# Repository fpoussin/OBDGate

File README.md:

# OBDGate
ELM327 compatible interface for motorcycle diagnostic interfaces (Honda, Kawasaki)

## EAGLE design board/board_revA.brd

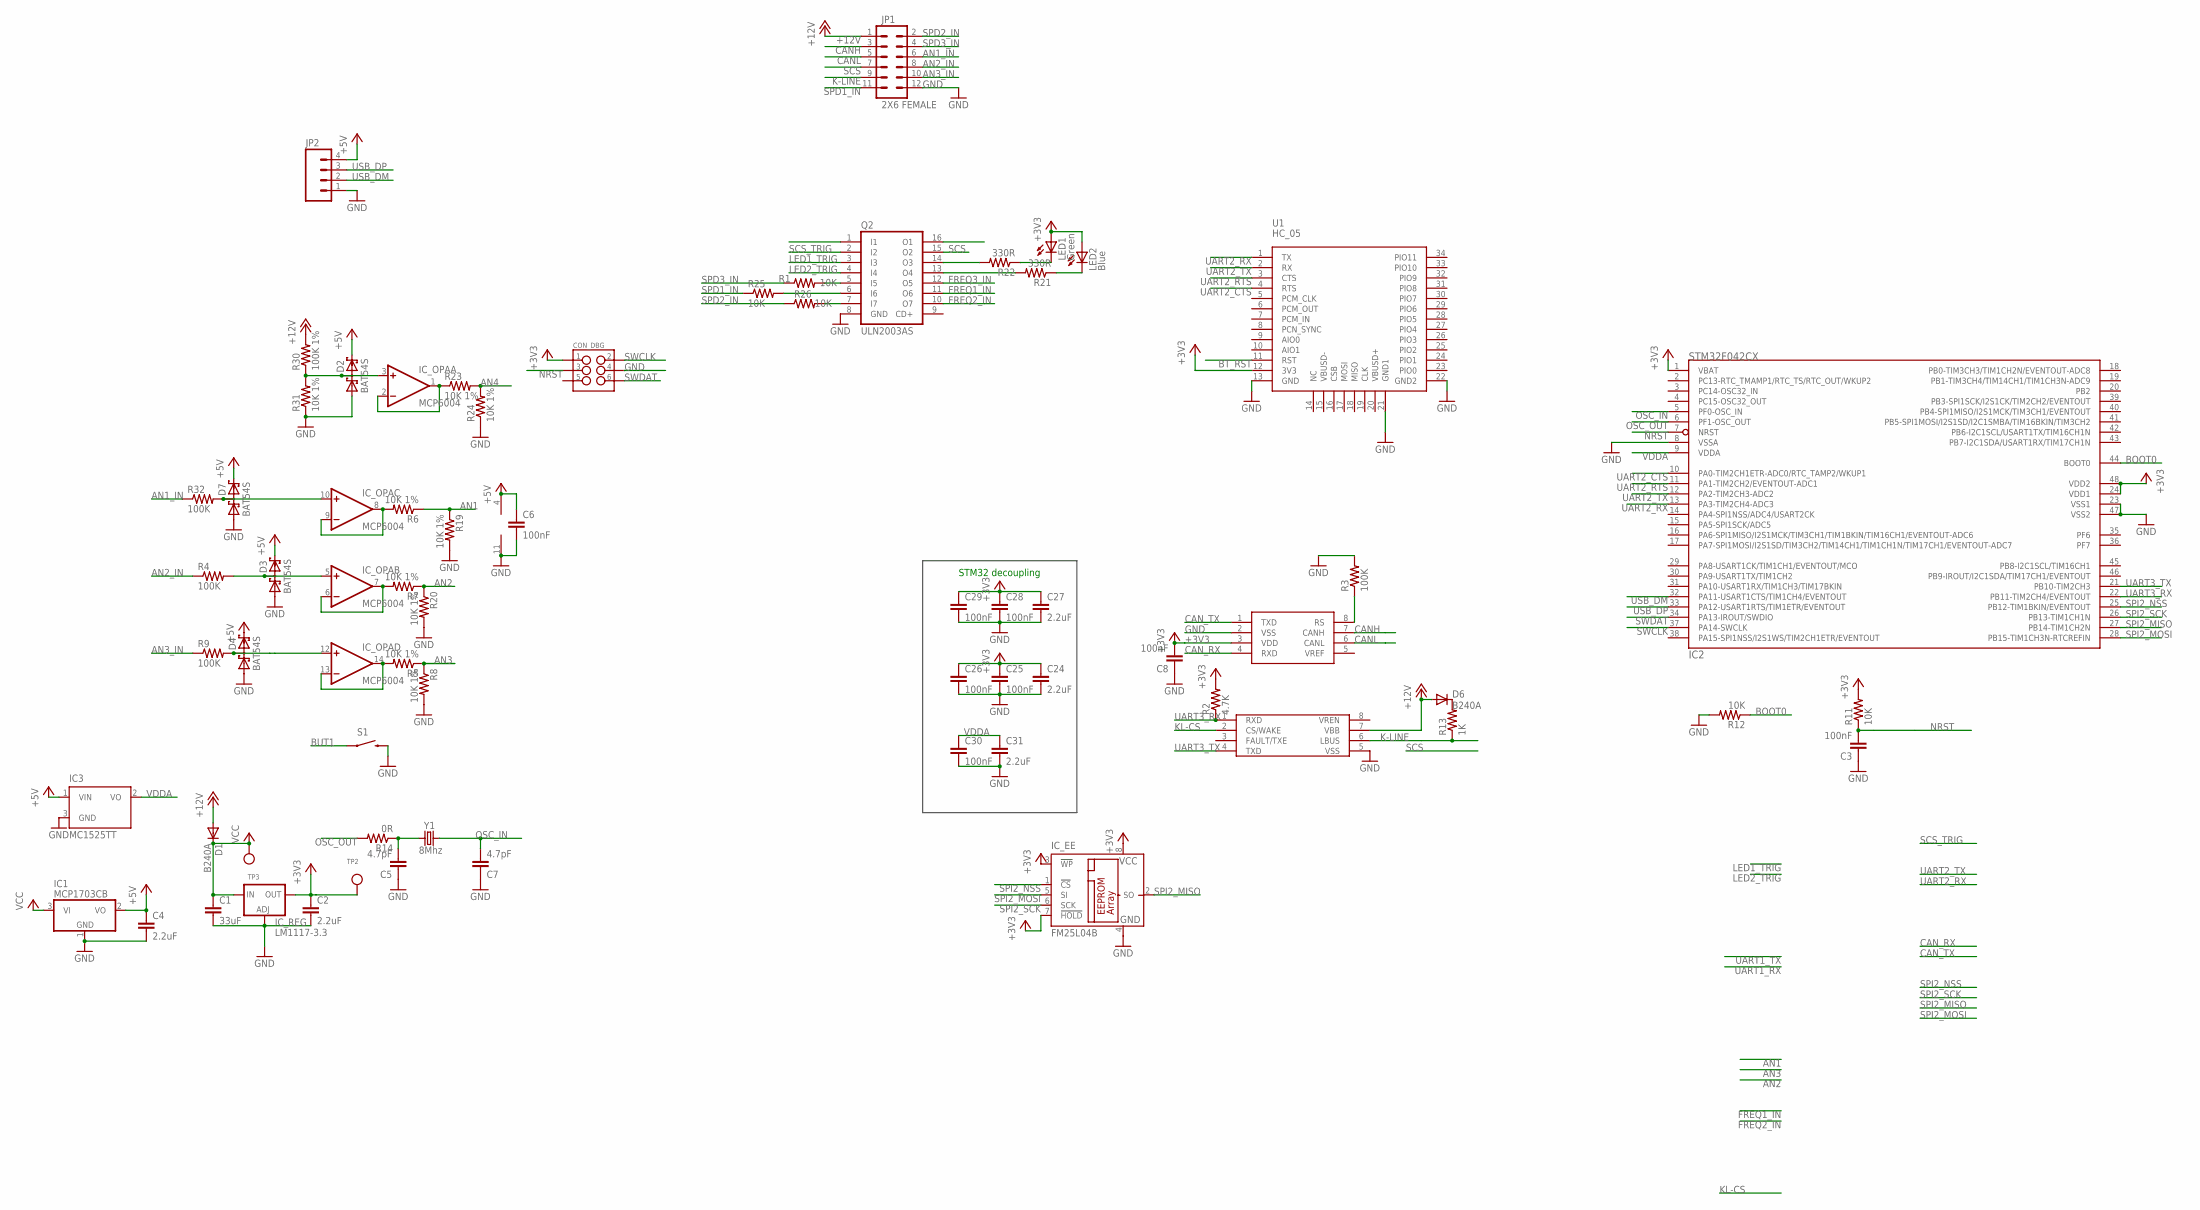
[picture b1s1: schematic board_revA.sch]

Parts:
C1: 33uF; CAP-PTH-SMALL
C2, C4, C24, C27, C31: 2.2uF; 0603-CAP
C3, C6, C8, C25, C26, C28, C29, C30: 100nF; 0603-CAP
C5, C7: 4.7pF; 0603-CAP
CON_DBG: M03X22X3_SILK_SM; 2X3
D1, D6: B240A; SOD-323
D2, D3, D4, D7: BAT54S; SOT23
IC1: MCP1703CB; SOT23
IC2: STM32F042CX; LQFP48
IC3: MC1525TT; SOT23
IC_CAN: MAX3051; SO08
IC_EE: FM25L04B; SO-08
IC_KLINE: MCP2004; SO08
IC_OPA: MCP6004; TSSOP14
IC_REG: LM1117-3.3; SOT223
JP1: 2X6 FEMALE; 2X6
JP2: M04LOCK; 1X04_LOCK
LED1: Green; LED3MM
LED2: Blue; LED3MM
Q2: ULN2003AS; SSOP16
R1, R11, R12, R25, R26: 10K; 0603-RES
R2: 4.7K; 0603-RES
R3, R4, R9, R32: 100K; 0603-RES
R5, R6, R7, R8, R19, R20, R23, R24, R31: 10K 1%; 0603-RES
R13: 1K; 0603-RES
R14: 0R; 0603-RES
R21, R22: 330R; 0603-RES
R30: 100K 1%; 0603-RES
S1: SWITCH-MOMENTARY-2PTH; TACTILE-PTH
TP2, TP3: TESTPOINTROUND1MM; TESTPOINT_ROUND_1MM
U1: HC_05; BLUETOOTH_SMD
Y1: 8Mhz; HC49US

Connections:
+3V3: C2.1, C8.2, C24.1, C25.1, C26.1, C27.1, C28.1, C29.1, CON_DBG.1, IC2.1 (VBAT), IC_CAN.3 (VDD), IC_EE.3 (!WP), IC_EE.7 (!HOLD), IC_EE.8 (VCC), IC_REG.4 (OUT), LED1.A, LED2.A, R2.2, R11.2, TP2.P$1, U1.12 (3V3)
+5V: C4.1, C6.1, D2.2 (C2), D3.2 (C2), D4.2 (C2), D7.2 (C2), IC1.2 (VO), IC3.1 (VIN), IC_OPA.4 (V+), JP2.4
+12V: D1.2 (A), D6.2 (A), IC_KLINE.7 (VBB), JP1.1, R30.2
AN1: R6.1, R19.1
AN1_IN: JP1.6, R32.1
AN1_N: IC_OPA.1 (OUT), IC_OPA.2 (-IN), R23.1
AN2: R7.1, R20.1
AN2_IN: JP1.8, R4.1
AN2_N: IC_OPA.8 (OUT), IC_OPA.9 (-IN), R6.2
AN3: R5.1, R8.1
AN3_IN: JP1.10, R9.1
AN3_N: IC_OPA.6 (-IN), IC_OPA.7 (OUT), R7.2
AN4: R23.2, R24.2
BOOT0: IC2.44 (BOOT0), R12.1
BT_RST: U1.11 (RST)
BUT1: S1.1
CANH: IC_CAN.7 (CANH), JP1.3
CANL: IC_CAN.6 (CANL), JP1.5
CAN_RX: IC_CAN.4 (RXD)
CAN_TX: IC_CAN.1 (TXD)
FREQ1_IN: Q2.11 (O6)
FREQ2_IN: Q2.10 (O7)
FREQ3_IN: Q2.12 (O5)
GND: C1.2, C2.2, C3.1, C4.2, C5.1, C6.2, C7.1, C8.1, C24.2, C25.2, C26.2, C27.2, C28.2, C29.2, C30.2, C31.2, CON_DBG.4, D2.1 (A1), D3.1 (A1), D4.1 (A1), D7.1 (A1), IC1.1 (GND), IC2.8 (VSSA), IC2.23 (VSS1), IC2.47 (VSS2), IC3.3 (GND), IC_CAN.2 (VSS), IC_EE.4 (GND), IC_KLINE.5 (VSS), IC_OPA.11 (V-), IC_REG.1 (ADJ), JP1.12, JP2.1, Q2.8 (GND), R3.2, R8.2, R12.2, R19.2, R20.2, R24.1, R31.1, S1.3 (2), U1.13 (GND), U1.21 (GND1), U1.22 (GND2)
K-LINE: IC_KLINE.6 (LBUS), JP1.9, R13.1
KL-CS: IC_KLINE.2 (CS/WAKE)
LED1_TRIG: Q2.3 (I3)
LED2_TRIG: Q2.4 (I4)
unnamed: Q2.5 (I5), R1.2
unnamed: IC_OPA.13 (-IN), IC_OPA.14 (OUT), R5.2
unnamed: D4.3 (C1A2), IC_OPA.12 (+IN), R9.2
unnamed: D3.3 (C1A2), IC_OPA.5 (+IN), R4.2
unnamed: IC_CAN.8 (RS), R3.1
unnamed: Q2.7 (I7), R26.2
unnamed: LED2.K (C), R21.1
unnamed: Q2.13 (O4), R21.2
unnamed: D6.1 (C), R13.2
unnamed: C5.2, R14.1, Y1.1
unnamed: Q2.14 (O3), R22.2
unnamed: Q2.6 (I6), R25.2
unnamed: LED1.K (C), R22.1
unnamed: D2.3 (C1A2), IC_OPA.3 (+IN), R30.1, R31.2
unnamed: D7.3 (C1A2), IC_OPA.10 (+IN), R32.2
NRST: C3.2, CON_DBG.3, IC2.7 (NRST), R11.1
OSC_IN: C7.2, IC2.5 (PF0-OSC_IN), Y1.2
OSC_OUT: IC2.6 (PF1-OSC_OUT), R14.2
SCS: JP1.7, Q2.15 (O2)
SCS_TRIG: Q2.2 (I2)
SPD1_IN: JP1.11, R25.1
SPD2_IN: JP1.2, R26.1
SPD3_IN: JP1.4, R1.1
SPI2_MISO: IC2.27 (PB14-TIM1CH2N), IC_EE.2 (SO)
SPI2_MOSI: IC2.28 (PB15-TIM1CH3N-RTCREFIN), IC_EE.5 (SI)
SPI2_NSS: IC2.25 (PB12-TIM1BKIN/EVENTOUT), IC_EE.1 (!CS)
SPI2_SCK: IC2.26 (PB13-TIM1CH1N), IC_EE.6 (SCK)
SWCLK: CON_DBG.2, IC2.37 (PA14-SWCLK)
SWDAT: CON_DBG.6, IC2.34 (PA13-IROUT/SWDIO)
UART2_CTS: IC2.10 (PA0-TIM2CH1ETR-ADC0/RTC_TAMP2/WKUP1), U1.4 (RTS)
UART2_RTS: IC2.11 (PA1-TIM2CH2/EVENTOUT-ADC1), U1.3 (CTS)
UART2_RX: IC2.13 (PA3-TIM2CH4-ADC3), U1.1 (TX)
UART2_TX: IC2.12 (PA2-TIM2CH3-ADC2), U1.2 (RX)
UART3_RX: IC2.22 (PB11-TIM2CH4/EVENTOUT), IC_KLINE.1 (RXD), R2.1
UART3_TX: IC2.21 (PB10-TIM2CH3), IC_KLINE.4 (TXD)
USB_DM: IC2.32 (PA11-USART1CTS/TIM1CH4/EVENTOUT), JP2.2
USB_DP: IC2.33 (PA12-USART1RTS/TIM1ETR/EVENTOUT), JP2.3
VCC: C1.1, D1.1 (C), IC1.3 (VI), IC_REG.3 (IN), TP3.P$1
VDD1: IC2.24 (VDD1), IC2.48 (VDD2)
VDDA: C30.1, C31.1, IC2.9 (VDDA), IC3.2 (VO)

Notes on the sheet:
STM32 decoupling

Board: 2 copper layers, 70 parts (6 on the bottom side), 57 nets, no tracks yet.

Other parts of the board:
U$2, U$3, U$4, U$5: 3,2
U$6: OSHW_FILLX500_NOTEXT

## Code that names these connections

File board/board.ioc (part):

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Mcu.Name=STM32F072C(8-B)Tx
Mcu.Package=LQFP48
Mcu.UserName=STM32F072CBTx
PA0.Mode=CTS_RTS
PA0.Signal=USART2_CTS
PA1.Mode=CTS_RTS
PA1.Signal=USART2_RTS
PA11.Mode=Device
PA11.Signal=USB_DM
PA12.Mode=Device
PA12.Signal=USB_DP
PA2.Mode=Asynchronous
PA2.Signal=USART2_TX
PA3.Mode=Asynchronous
PA3.Signal=USART2_RX
PB10.Mode=Asynchronous
PB10.Signal=USART3_TX
PB11.Mode=Asynchronous
PB11.Signal=USART3_RX
PB12.Mode=NSS_Signal_Hard
PB12.Signal=SPI2_NSS
PB13.Mode=Full_Duplex_Master
PB13.Signal=SPI2_SCK
PB14.Mode=Full_Duplex_Master
PB14.Signal=SPI2_MISO
PB15.Mode=Full_Duplex_Master
PB15.Signal=SPI2_MOSI
PB8.Mode=Master
PB8.Signal=CAN_RX
PB9.Mode=Master
PB9.Signal=CAN_TX

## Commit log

2015-10-02 [Board] Cleaning, WIP
2015-10-03 [Board] Working on schema
2015-10-03 [Board] WIP

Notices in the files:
parts and their libraries:
SparkFun-Passives: Licensing: CC v3.0 Share-Alike You are welcome to use this library for commercial purposes.
microbuilder: This work is placed in the public domain, and may be freely used for commercial and non-commercial work with the following conditions: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
